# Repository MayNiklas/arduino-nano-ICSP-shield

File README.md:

# arduino-nano-ICSP-shield

A simple shield, that exposes a 6 pin ICSP header to use an Arduino Nano as a ISP programmer.

## BOM

Interactive BOM available: https://mayniklas.github.io/arduino-nano-ICSP-shield/

I'm linking the products I'm testing with, not the ones I recommend.

* 1x [Arduino Nano](https://www.aliexpress.com/item/1005007392605300.html?spm=a2g0o.order_list.order_list_main.17.49c7180237FQjT)
* 1x [6 pin 2x3 IDC3 Box Headers](https://www.aliexpress.com/item/1005007470581902.html)
* 1x [6 pin 2x3 Pitch JTAG ISP Ribbon Cable](https://www.aliexpress.com/item/1005004762590129.html)
* 1x [0603 SMD - 10µF electrolytic capacitor](https://www.lcsc.com/product-detail/Multilayer-Ceramic-Capacitors-MLCC-SMD-SMT_Samsung-Electro-Mechanics-CL10A106KP8NNNC_C19702.html)
* 3x [0603 SMD - LED](https://www.lcsc.com/product-detail/LED-Indication-Discrete_XINGLIGHT-XL-1608SURC-06_C965799.html)
* 3x [0603 SMD - 470 Ohm Resistor](https://www.lcsc.com/product-detail/Chip-Resistor-Surface-Mount_UNI-ROYAL-Uniroyal-Elec-0603WAF4700T5E_C23179.html)

## Documentation

* [Arduino as ISP](https://docs.arduino.cc/built-in-examples/arduino-isp/ArduinoISP/)

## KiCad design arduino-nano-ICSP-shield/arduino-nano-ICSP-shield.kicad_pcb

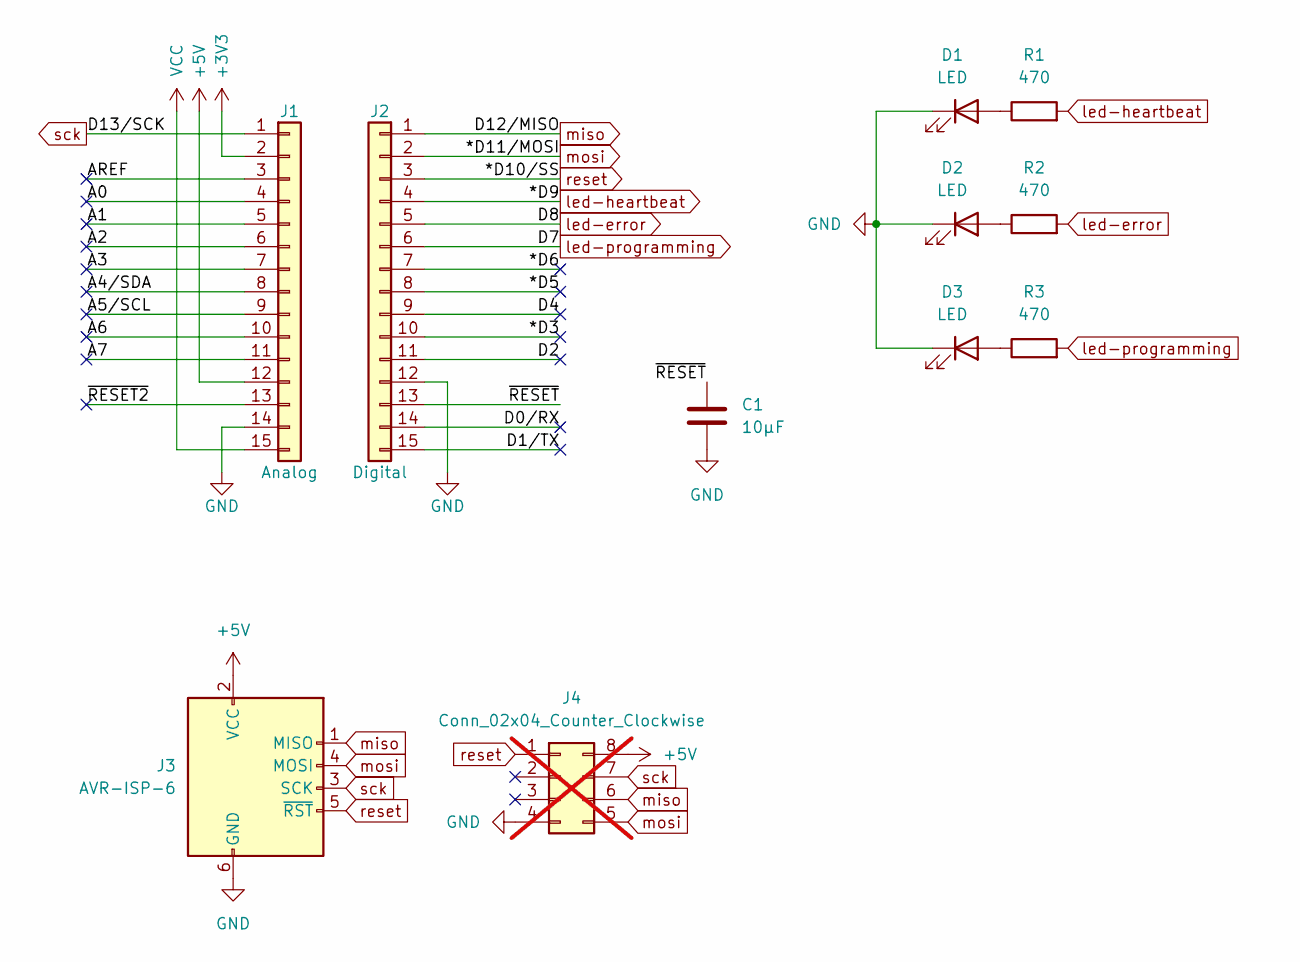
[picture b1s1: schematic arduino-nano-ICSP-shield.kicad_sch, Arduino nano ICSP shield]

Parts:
C1: 10µF; C_0603_1608Metric; LCSC C19702
D1, D2, D3: LED; LED_0603_1608Metric; LCSC C965799
J1: Analog; PinHeader_1x15_P2.54mm_Vertical
J2: Digital; PinHeader_1x15_P2.54mm_Vertical
J3: AVR-ISP-6; IDC-Header_2x03_P2.54mm_Vertical-ICSP-6; LCSC C7430309
J4: Conn_02x04_Counter_Clockwise; PinHeader_2x04_P2.54mm_Vertical_Counterclockwise-Clip; not fitted
R1, R2, R3: 470; R_0603_1608Metric; LCSC C23179

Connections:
+3V3: J1.2
+5V: J1.12, J3.2 (VCC), J4.8
/*D3: J2.10
/*D5: J2.8
/*D6: J2.7
/A0: J1.4
/A1: J1.5
/A2: J1.6
/A3: J1.7
/A4/SDA: J1.8
/A5/SCL: J1.9
/A6: J1.10
/A7: J1.11
/AREF: J1.3
/D0/RX: J2.14
/D1/TX: J2.15
/D2: J2.11
/D4: J2.9
/~RESET2: J1.13
/~RESET: C1.1, J2.13
GND: C1.2, D1.1 (K), D2.1 (K), D3.1 (K), J1.14, J2.12, J3.6 (GND), J4.4
unnamed: D1.2 (A), R1.1
unnamed: D2.2 (A), R2.1
unnamed: D3.2 (A), R3.1
VCC: J1.15
led-error: J2.5, R2.2
led-heartbeat: J2.4, R1.2
led-programming: J2.6, R3.2
miso: J2.1, J3.1 (MISO), J4.6
mosi: J2.2, J3.4 (MOSI), J4.5
reset: J2.3, J3.5 (~RST), J4.1
sck: J1.1, J3.3 (SCK), J4.7

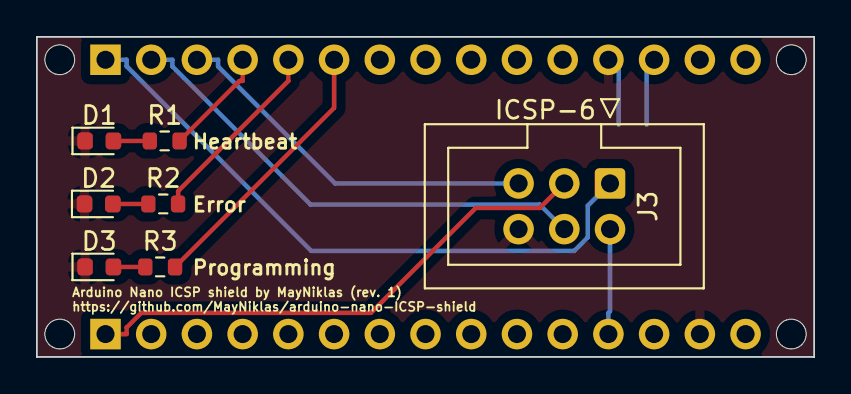
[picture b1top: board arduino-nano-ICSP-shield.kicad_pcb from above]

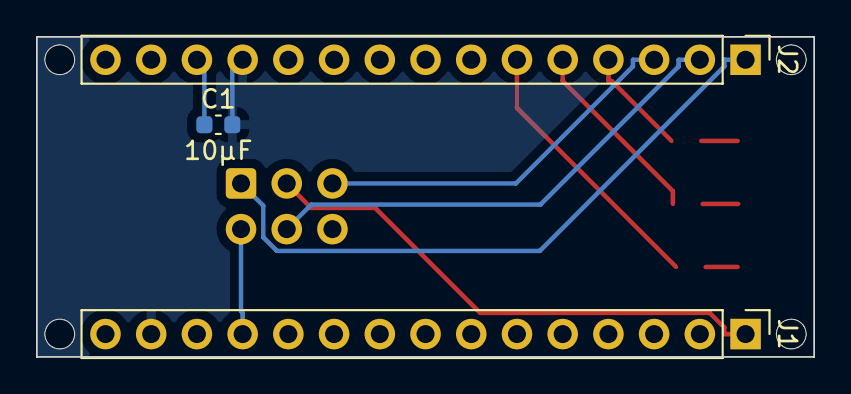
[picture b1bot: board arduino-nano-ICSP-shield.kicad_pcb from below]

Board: 2 copper layers, 43.2 x 17.8 mm, 14 parts (3 on the bottom side), 13 nets.

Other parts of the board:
MH1, MH2, MH3, MH4: MountingHole_65mil

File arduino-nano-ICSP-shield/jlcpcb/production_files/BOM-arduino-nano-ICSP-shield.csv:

Comment,Designator,Footprint,LCSC,Quantity
10µF,C1,C_0603_1608Metric,C19702,1
470,"R1,R2,R3",R_0603_1608Metric,C23179,3
LED,"D1,D2,D3",LED_0603_1608Metric,C965799,3
AVR-ISP-6,J3,IDC-Header_2x03_P2.54mm_Vertical-ICSP-6,,1
Analog,J1,PinHeader_1x15_P2.54mm_Vertical,,1
Digital,J2,PinHeader_1x15_P2.54mm_Vertical,,1

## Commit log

2025-03-07 init
2025-03-07 init led's
2025-03-08 add ports
2025-03-08 rename header
2025-03-08 single header
2025-03-08 print 10µF
2025-03-08 stuff
2025-03-08 green
2025-03-08 add README
2025-03-08 continue
2025-03-09 move parts to the back
2025-03-09 add jlcpcb folder
2025-03-09 remove linked pins & route
2025-03-09 add 140 Ohm resistor to the components list and remove 150 Ohm resistor
2025-03-09 flip resistor
2025-03-09 routed by hand
2025-03-09 add no_connect
2025-03-09 3 different resistors
2025-03-09 Readd Clip
2025-03-09 improv
2025-03-10 split RESET into RESET & RESET2
2025-03-10 add ttle
2025-03-10 add text
2025-03-10 move text down
2025-03-10 add led- to label name
2025-03-10 change color
2025-03-10 move condensator
2025-03-10 set lcsc id's
2025-03-11 export project
2025-03-11 create ibom
2025-03-11 move
2025-03-12 reference only once
2025-03-15 add pictures
2025-03-15 add caution
2025-03-15 update parts list
2025-03-15 split line
2025-03-16 deploy using GitHub actions
2025-04-26 add LCSC property to schematic
2025-04-26 changes caused by updates in KiCad
2025-04-26 switch to using KiBot
2025-04-26 add LCSC # for 10uF
2025-08-15 add definitions for footprint values in KiBot configuration
2025-08-15 add release action
2025-08-15 remove disclaimer
2025-08-15 Bump actions/checkout from 4 to 5
    Bumps [actions/checkout](https://github.com/actions/checkout) from 4 to 5.
    - [Release notes](https://github.com/actions/checkout/releases)
    - [Changelog](https://github.com/actions/checkout/blob/main/CHANGELOG.md)
    - [Commits](https://github.com/actions/checkout/compare/v4...v5)
    ---
    updated-dependencies:
2025-08-15 kibot: generate Diff
2025-08-15 kibot: add renders
2025-08-15 remove render_3d
2025-08-26 Bump actions/upload-pages-artifact from 3 to 4
    Bumps [actions/upload-pages-artifact](https://github.com/actions/upload-pages-artifact) from 3 to 4.
    - [Release notes](https://github.com/actions/upload-pages-artifact/releases)
    - [Commits](https://github.com/actions/upload-pages-artifact/compare/v3...v4)
    ---
    updated-dependencies:
    - dependency-name: actions/upload-pages-artifact
2025-10-27 Bump actions/download-artifact from 5 to 6
    Bumps [actions/download-artifact](https://github.com/actions/download-artifact) from 5 to 6.
    - [Release notes](https://github.com/actions/download-artifact/releases)
    - [Commits](https://github.com/actions/download-artifact/compare/v5...v6)
    ---
    updated-dependencies:
    - dependency-name: actions/download-artifact
2025-10-27 Bump actions/upload-artifact from 4 to 5
    Bumps [actions/upload-artifact](https://github.com/actions/upload-artifact) from 4 to 5.
    - [Release notes](https://github.com/actions/upload-artifact/releases)
    - [Commits](https://github.com/actions/upload-artifact/compare/v4...v5)
    ---
    updated-dependencies:
    - dependency-name: actions/upload-artifact
2025-11-24 Bump actions/checkout from 5 to 6
    Bumps [actions/checkout](https://github.com/actions/checkout) from 5 to 6.
    - [Release notes](https://github.com/actions/checkout/releases)
    - [Changelog](https://github.com/actions/checkout/blob/main/CHANGELOG.md)
    - [Commits](https://github.com/actions/checkout/compare/v5...v6)
    ---
    updated-dependencies:
2025-12-15 Bump actions/download-artifact from 5 to 7
    Bumps [actions/download-artifact](https://github.com/actions/download-artifact) from 5 to 7.
    - [Release notes](https://github.com/actions/download-artifact/releases)
    - [Commits](https://github.com/actions/download-artifact/compare/v5...v7)
    ---
    updated-dependencies:
    - dependency-name: actions/download-artifact
2025-12-15 Bump actions/upload-artifact from 4 to 6
    Bumps [actions/upload-artifact](https://github.com/actions/upload-artifact) from 4 to 6.
    - [Release notes](https://github.com/actions/upload-artifact/releases)
    - [Commits](https://github.com/actions/upload-artifact/compare/v4...v6)
    ---
    updated-dependencies:
    - dependency-name: actions/upload-artifact
